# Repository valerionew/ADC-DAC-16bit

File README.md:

# ADC-DAC-16bit

Released under CC-BY-SA 4.0 license  

### Project status
At this time, the board is mounted and waiting to be tested 

### Project description 
An easy and cheap board to prototypate with two dual channel 16 bit A/D and D/A converters.  
Makes use of I2C to communicate with a microcontroller, see the datasheets for reference.  
Drawn in KiCAD.

Makes use of:
* **MCP3426** 16 bit ADC, dual channel, differential
* **AD5667R** 16 bit DAC, dual channel (the R at the end is important)
* 2 100nF 0603 capacitors
* 2 100nF 0805 capacitors
* 2 10uF  1206 capacitors
* 2 4k7   0805 resistors  

But look how cute it is

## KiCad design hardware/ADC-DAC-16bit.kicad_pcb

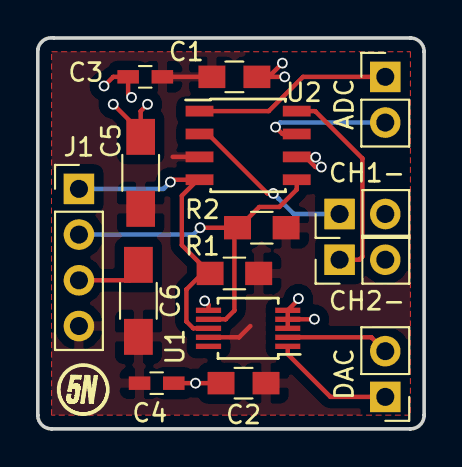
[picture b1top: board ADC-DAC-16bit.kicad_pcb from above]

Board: 2 copper layers, 21.5 x 21.7 mm, 15 parts (0 on the bottom side), 10 nets.

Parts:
C1, C2: 100n; C_0805_HandSoldering
C3, C4: 100n; C_0603_HandSoldering
C5, C6: 10u; C_1206_HandSoldering
J1: CON; Pin_Header_Straight_1x04_Pitch2.54mm
J2: DAC; Pin_Header_Straight_1x02_Pitch2.54mm
J3: ADC; Pin_Header_Straight_1x02_Pitch2.54mm
J4: CH1-; Pin_Header_Straight_1x02_Pitch2.54mm
J5: CH2-; Pin_Header_Straight_1x02_Pitch2.54mm
R1, R2: 4K7; R_0805_HandSoldering
U1: AD5667R; MSOP-10_3x3mm_Pitch0.5mm
U2: MCP3426; SOIC-8_3.9x4.9mm_Pitch1.27mm

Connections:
+5V: C1.1, C2.1, C3.1, C4.1, C5.1, C6.1, J1.4, R1.1, R2.1, U1.9, U2.3
GND: C1.2, C2.2, C3.2, C4.2, C5.2, C6.2, J1.3, J4.2, J5.2, U1.3, U1.4, U1.5, U1.6, U2.6
unnamed: J1.1, R1.2, U1.8, U2.4
unnamed: J1.2, R2.2, U1.7, U2.5
unnamed: J2.1, U1.1
unnamed: J2.2, U1.2
unnamed: J3.1, U2.1
unnamed: J3.2, U2.7
unnamed: J4.1, U2.2
unnamed: J5.1, U2.8

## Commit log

2017-06-03 Added project files
2017-06-04 Added 3D view image
2017-07-17 moved file
2017-07-17 Rename ADC-DAC-16bit.kicad_pcb to hardware/ADC-DAC-16bit.kicad_pcb
2017-07-17 v0.2 update
2017-07-21 First commit, NOT TESTED!
2017-07-29 changed static method to normal method, ivin possibility to override the default i2c address.

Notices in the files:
README.md:
License: CC BY-SA 4.0
